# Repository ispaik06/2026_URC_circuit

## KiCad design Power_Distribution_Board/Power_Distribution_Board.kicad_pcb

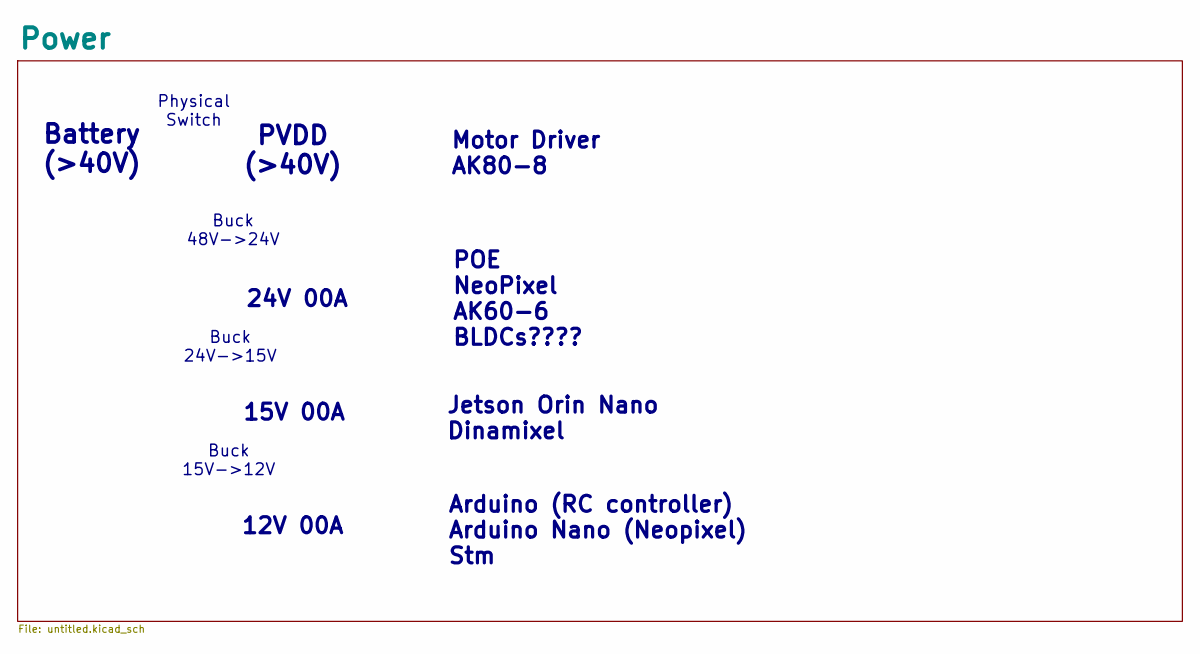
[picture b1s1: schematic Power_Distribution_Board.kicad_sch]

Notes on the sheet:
Jetson Orin Nano Dinamixel
Motor Driver AK80-8
Arduino (RC controller) Arduino Nano (Neopixel) Stm
Buck 15V->12V
POE NeoPixel AK60-6 BLDCs????
15V 00A
Physical Switch
Buck 48V->24V
24V 00A
12V 00A
Buck 24V->15V
PVDD (>40V)
Battery (>40V)

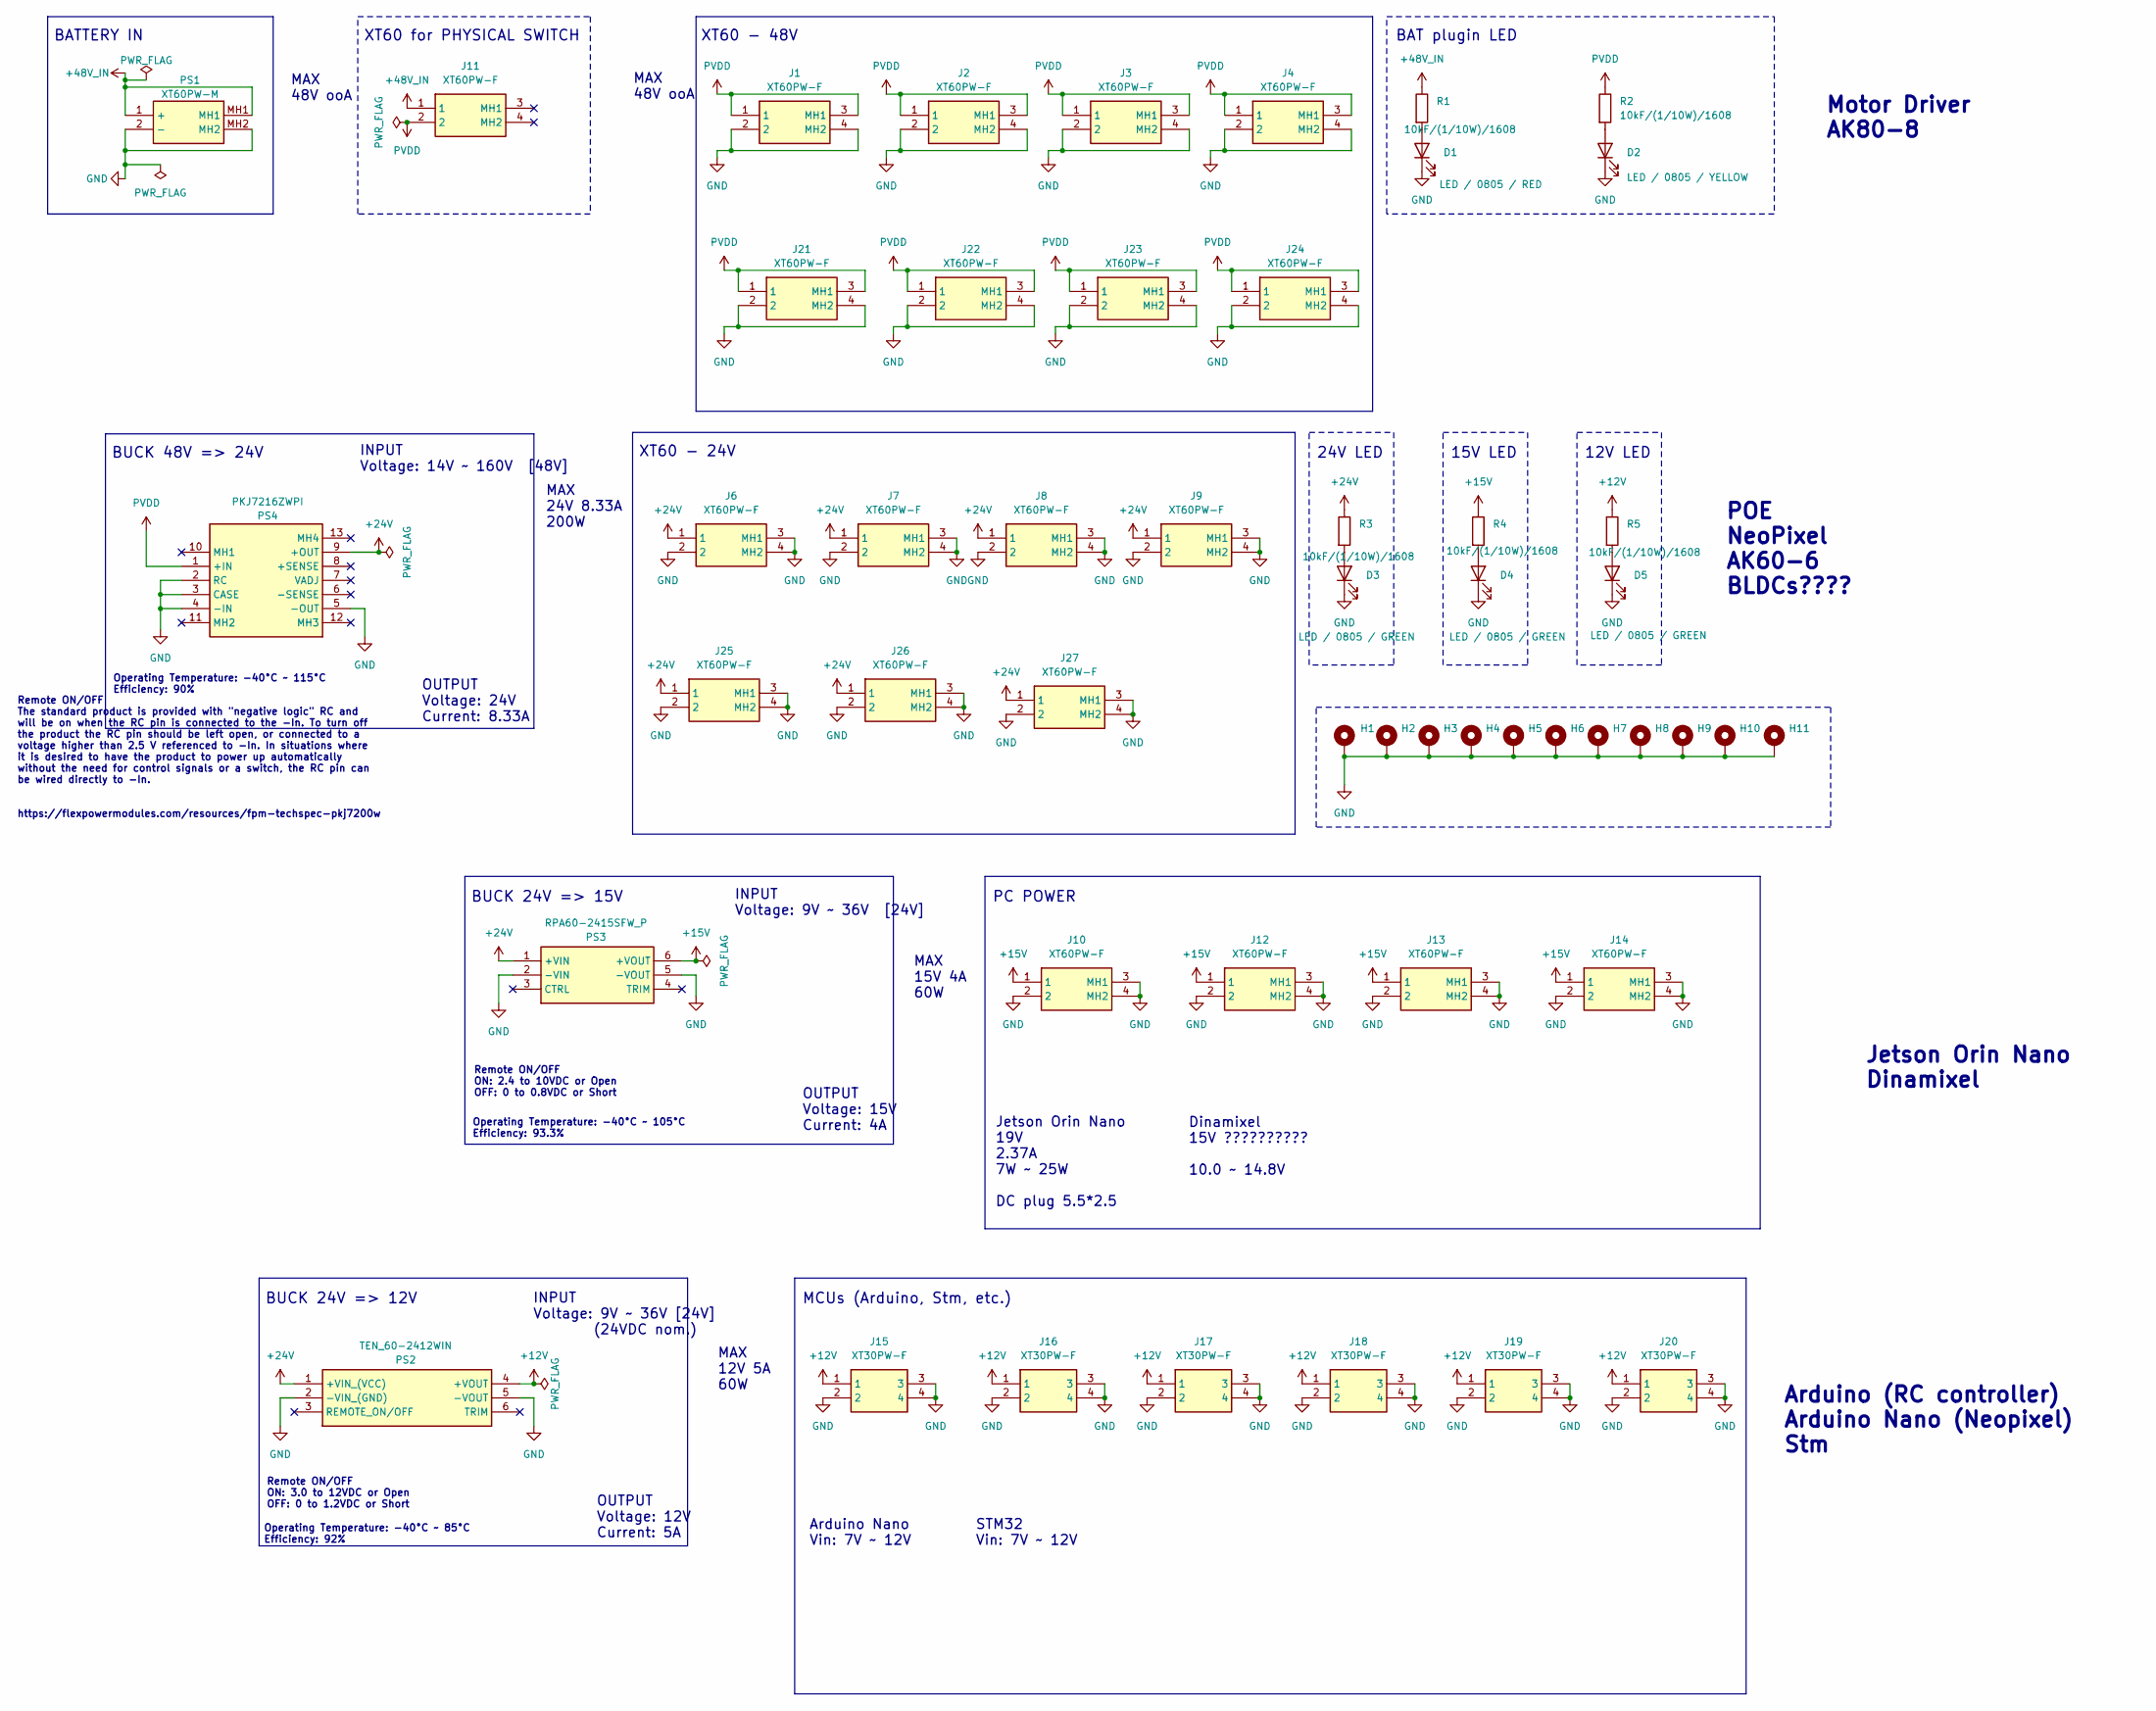
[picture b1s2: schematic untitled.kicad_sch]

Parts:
D1: LED / 0805 / RED; LED_0805_2012Metric
D2: LED / 0805 / YELLOW; LED_0805_2012Metric
D3, D4, D5: LED / 0805 / GREEN; LED_0805_2012Metric
H1, H2, H3, H4, H5, H6, H7, H8, H9, H10, H11: MountingHole_Pad; MountingHole_3.2mm_M3_Pad
J1, J2, J3, J4, J6, J7, J8, J9, J10, J11, J12, J13, J14, J21, J22, J23, J24, J25, J26, J27: XT60PW-F; XT60PWF; Manufacturer_Part_Number XT60PW-F
J15, J16, J17, J18, J19, J20: XT30PW-F; XT30PWF; Manufacturer_Part_Number XT30PW-F
PS1: XT60PW-M; XT60PWM; Manufacturer_Part_Number XT60PW-M
PS2: TEN_60-2412WIN; TEN602425WIN; Manufacturer_Part_Number TEN 60-2412WIN; Mouser Part Number 495-TEN-60-2412WIN
PS3: RPA60-2415SFW_P; RPA602415SFWP; Manufacturer_Part_Number RPA60-2415SFW/P; Mouser Part Number 919-RPA60-2415SFW/P
PS4: PKJ7216ZWPI; Manufacturer_Part_Number PKJ7216ZWPI
R1, R2, R3, R4, R5: 10kF/(1/10W)/1608; R_0603_1608Metric

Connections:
+12V: J15.1, J16.1, J17.1, J18.1, J19.1, J20.1, PS2.4 (+VOUT), R5.1
+15V: J10.1, J12.1, J13.1, J14.1, PS3.6 (+VOUT), R4.1
+24V: J6.1, J7.1, J8.1, J9.1, J25.1, J26.1, J27.1, PS2.1 (+VIN_(VCC)), PS3.1 (+VIN), PS4.9 (+OUT), R3.1
+48V_IN: J11.1, PS1.1 (+), PS1.MH1, R1.1
GND: D1.1 (K), D2.1 (K), D3.1 (K), D4.1 (K), D5.1 (K), H1.1, H2.1, H3.1, H4.1, H5.1, H6.1, H7.1, H8.1, H9.1, H10.1, H11.1, J1.2, J1.4 (MH2), J2.2, J2.4 (MH2), J3.2, J3.4 (MH2), J4.2, J4.4 (MH2), J6.2, J6.3 (MH1), J6.4 (MH2), J7.2, J7.3 (MH1), J7.4 (MH2), J8.2, J8.3 (MH1), J8.4 (MH2), J9.2, J9.3 (MH1), J9.4 (MH2), J10.2, J10.3 (MH1), J10.4 (MH2), J12.2, J12.3 (MH1), J12.4 (MH2), J13.2, J13.3 (MH1), J13.4 (MH2), J14.2, J14.3 (MH1), J14.4 (MH2), J15.2, J15.3, J15.4, J16.2, J16.3, J16.4, J17.2, J17.3, J17.4, J18.2, J18.3, J18.4, J19.2, J19.3, J19.4, J20.2, J20.3, J20.4, J21.2, J21.4 (MH2), J22.2, J22.4 (MH2), J23.2, J23.4 (MH2), J24.2, J24.4 (MH2), J25.2, J25.3 (MH1), J25.4 (MH2), J26.2, J26.3 (MH1), J26.4 (MH2), J27.2, J27.3 (MH1), J27.4 (MH2), PS1.2 (-), PS1.MH2, PS2.2 (-VIN_(GND)), PS2.5 (-VOUT), PS3.2 (-VIN), PS3.5 (-VOUT), PS4.2 (RC), PS4.3 (CASE), PS4.4 (-IN), PS4.5 (-OUT)
unnamed: D1.2 (A), R1.2
unnamed: D2.2 (A), R2.2
unnamed: D3.2 (A), R3.2
unnamed: D4.2 (A), R4.2
unnamed: D5.2 (A), R5.2
PVDD: J1.1, J1.3 (MH1), J2.1, J2.3 (MH1), J3.1, J3.3 (MH1), J4.1, J4.3 (MH1), J11.2, J21.1, J21.3 (MH1), J22.1, J22.3 (MH1), J23.1, J23.3 (MH1), J24.1, J24.3 (MH1), PS4.1 (+IN), R2.1

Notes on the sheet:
OUTPUT Voltage: 24V Current: 8.33A
MAX 48V ooA
PC POWER
MAX 24V 8.33A 200W
Arduino (RC controller) Arduino Nano (Neopixel) Stm
INPUT Voltage: 14V ~ 160V [48V]
BUCK 48V => 24V
Jetson Orin Nano 19V 2.37A 7W ~ 25W DC plug 5.5*2.5
Jetson Orin Nano Dinamixel
Remote ON/OFF ON: 3.0 to 12VDC or Open OFF: 0 to 1.2VDC or Short
INPUT Voltage: 9V ~ 36V [24V]
Dinamixel 15V ?????????? 10.0 ~ 14.8V
Operating Temperature: -40°C ~ 85°C Efficiency: 92%
Operating Temperature: -40°C ~ 115°C Efficiency: 90%
Operating Temperature: -40°C ~ 105°C Efficiency: 93.3%
MAX 15V 4A 60W
POE NeoPixel AK60-6 BLDCs????
OUTPUT Voltage: 12V Current: 5A
STM32 Vin: 7V ~ 12V
BUCK 24V => 15V
XT60 - 24V
24V LED
XT60 for PHYSICAL SWITCH
Arduino Nano Vin: 7V ~ 12V
Remote ON/OFF ON: 2.4 to 10VDC or Open OFF: 0 to 0.8VDC or Short
Remote ON/OFF The standard product is provided with "negative logic" RC and will be on when the RC pin is connected to the -In. To turn off the product the RC pin should be left open, or connected to a voltage higher than 2.5 V referenced to -In. In situations where it is desired to have the produc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
Motor Driver AK80-8
BAT plugin LED
BATTERY IN
MAX 12V 5A 60W
XT60 - 48V
OUTPUT Voltage: 15V Current: 4A
15V LED
INPUT Voltage: 9V ~ 36V [24V] (24VDC nom.)
12V LED
MCUs (Arduino, Stm, etc.)
BUCK 24V => 12V

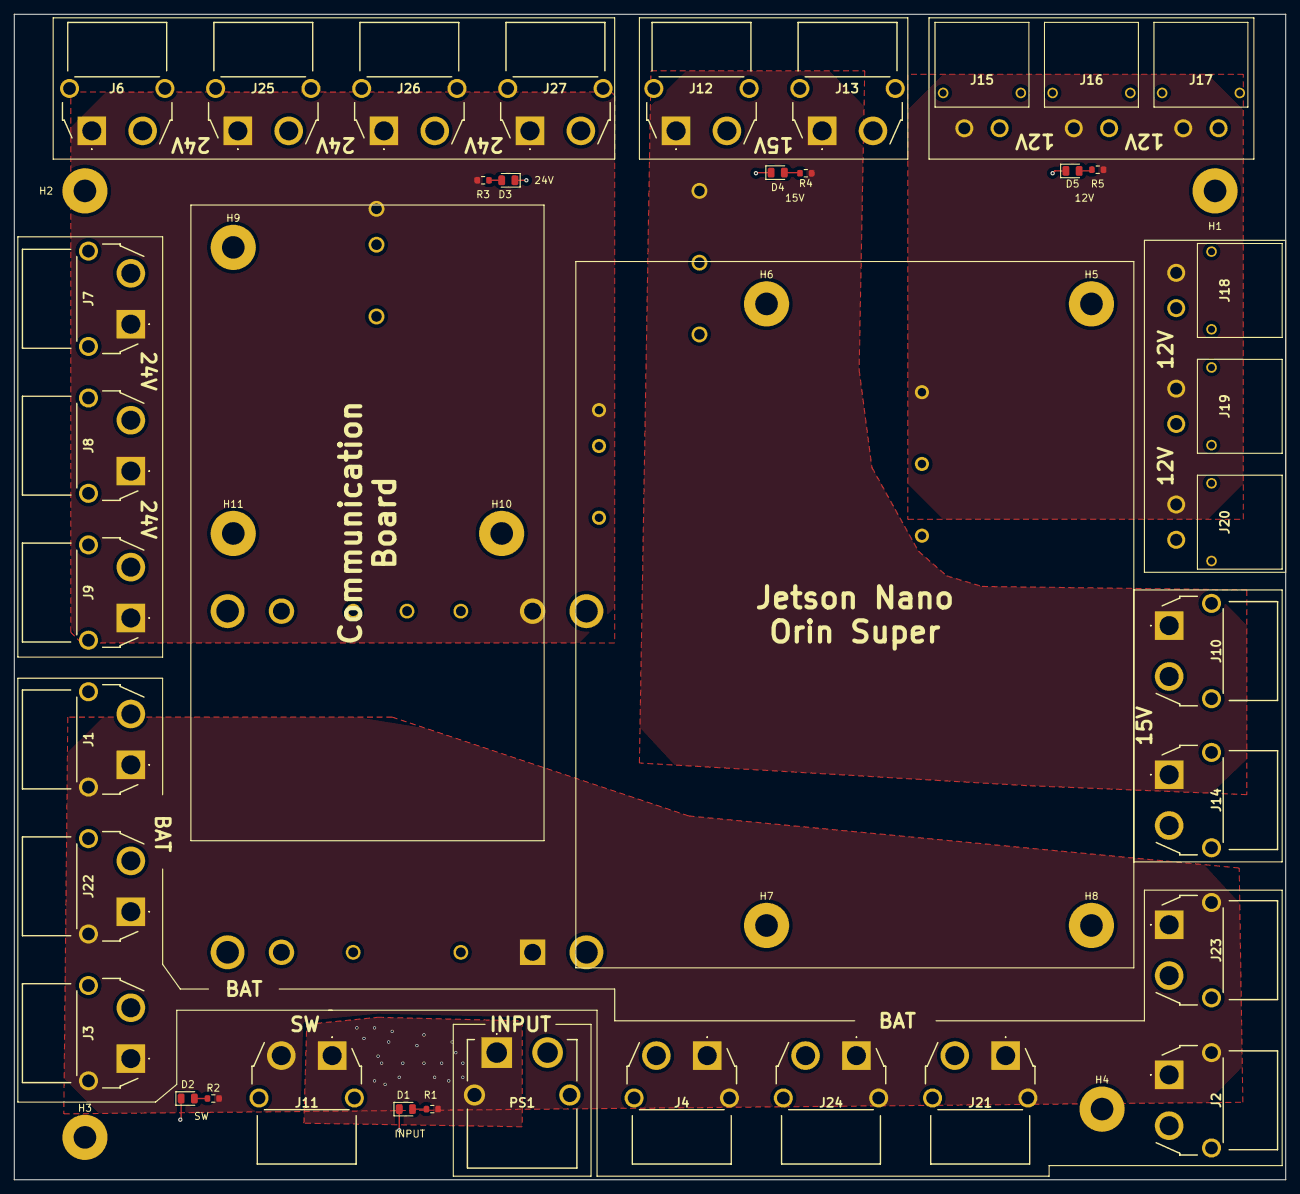
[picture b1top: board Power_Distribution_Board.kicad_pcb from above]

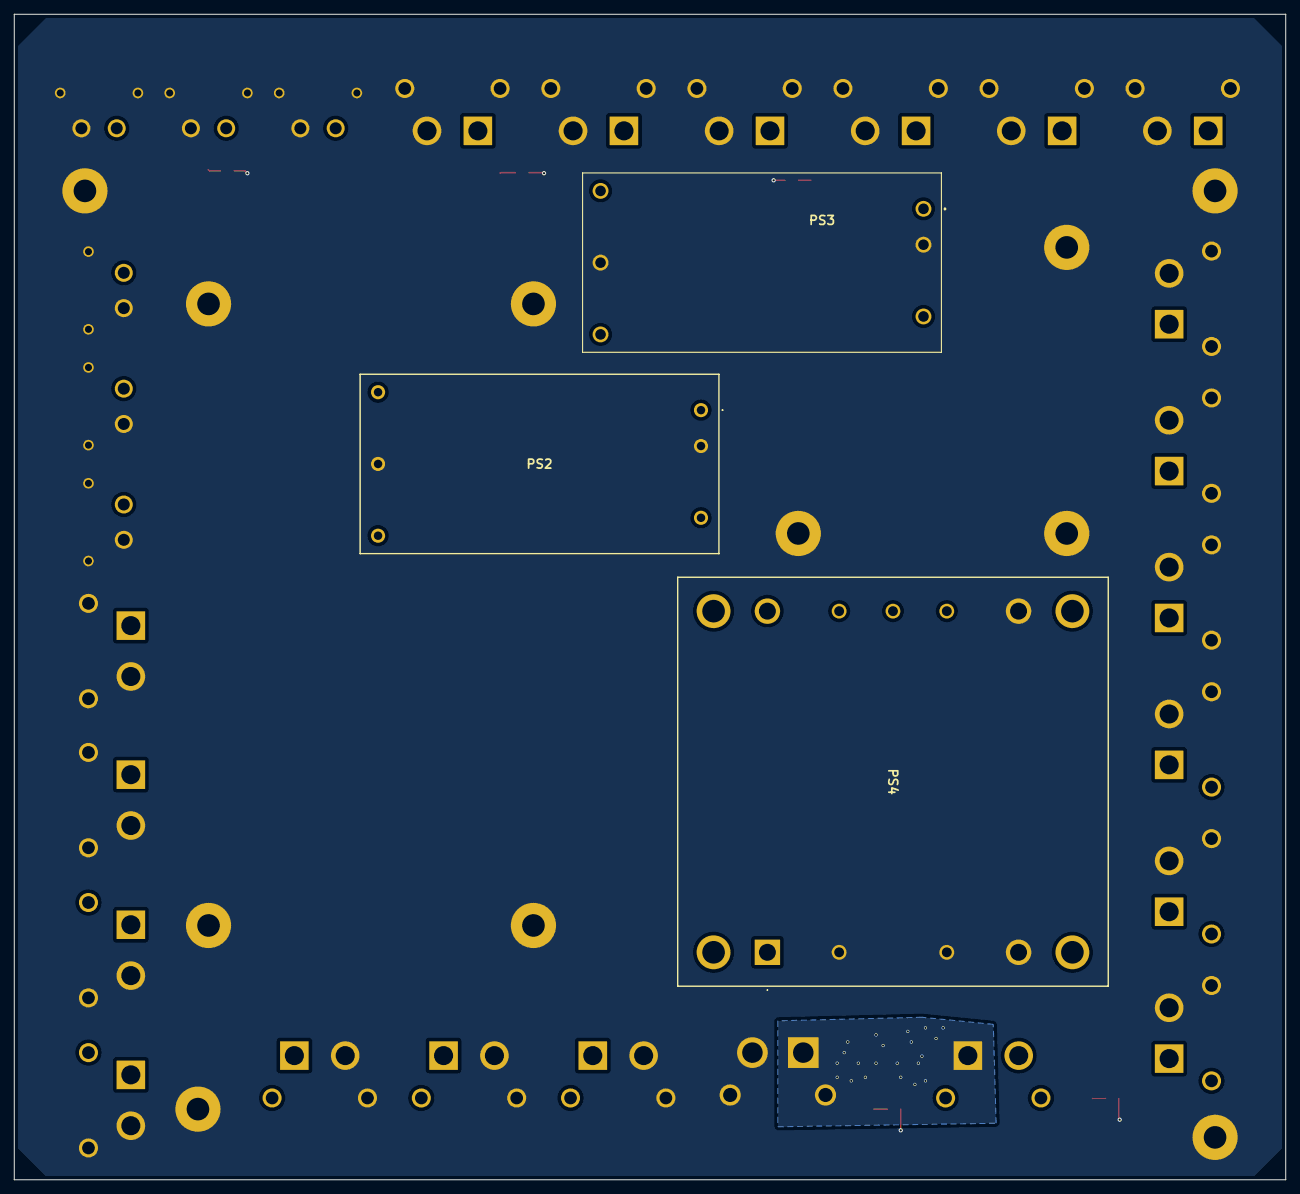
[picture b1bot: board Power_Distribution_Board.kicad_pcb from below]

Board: 2 copper layers, 180.0 x 165.0 mm, 51 parts (3 on the bottom side), 11 nets.

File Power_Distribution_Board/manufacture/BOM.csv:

"Reference","Qty","Value"
"D1","1","LED / 0805 / RED"
"D2","1","LED / 0805 / YELLOW"
"D3,D4,D5","3","LED / 0805 / GREEN"
"H1,H2,H3,H4,H5,H6,H7,H8,H9,H10","10","MountingHole_Pad"
"R1,R2,R3,R4,R5","5","10kF/(1/10W)/1608"
"J5","1","DCM3623T75H26C2T00"
"PS3","1","RPA60-2415SFW_P"
"PS2","1","TEN_60-2412WIN"
"J15,J16,J17,J18,J19,J20","6","XT30PW-F"
"J1,J2,J3,J4,J6,J7,J8,J9,J10,J11,J12,J13,J14,J21,J22,J23,J24,J25,J26,J27","20","XT60PW-F"
"PS1","1","XT60PW-M"

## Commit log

2025-07-25 Buck changed
